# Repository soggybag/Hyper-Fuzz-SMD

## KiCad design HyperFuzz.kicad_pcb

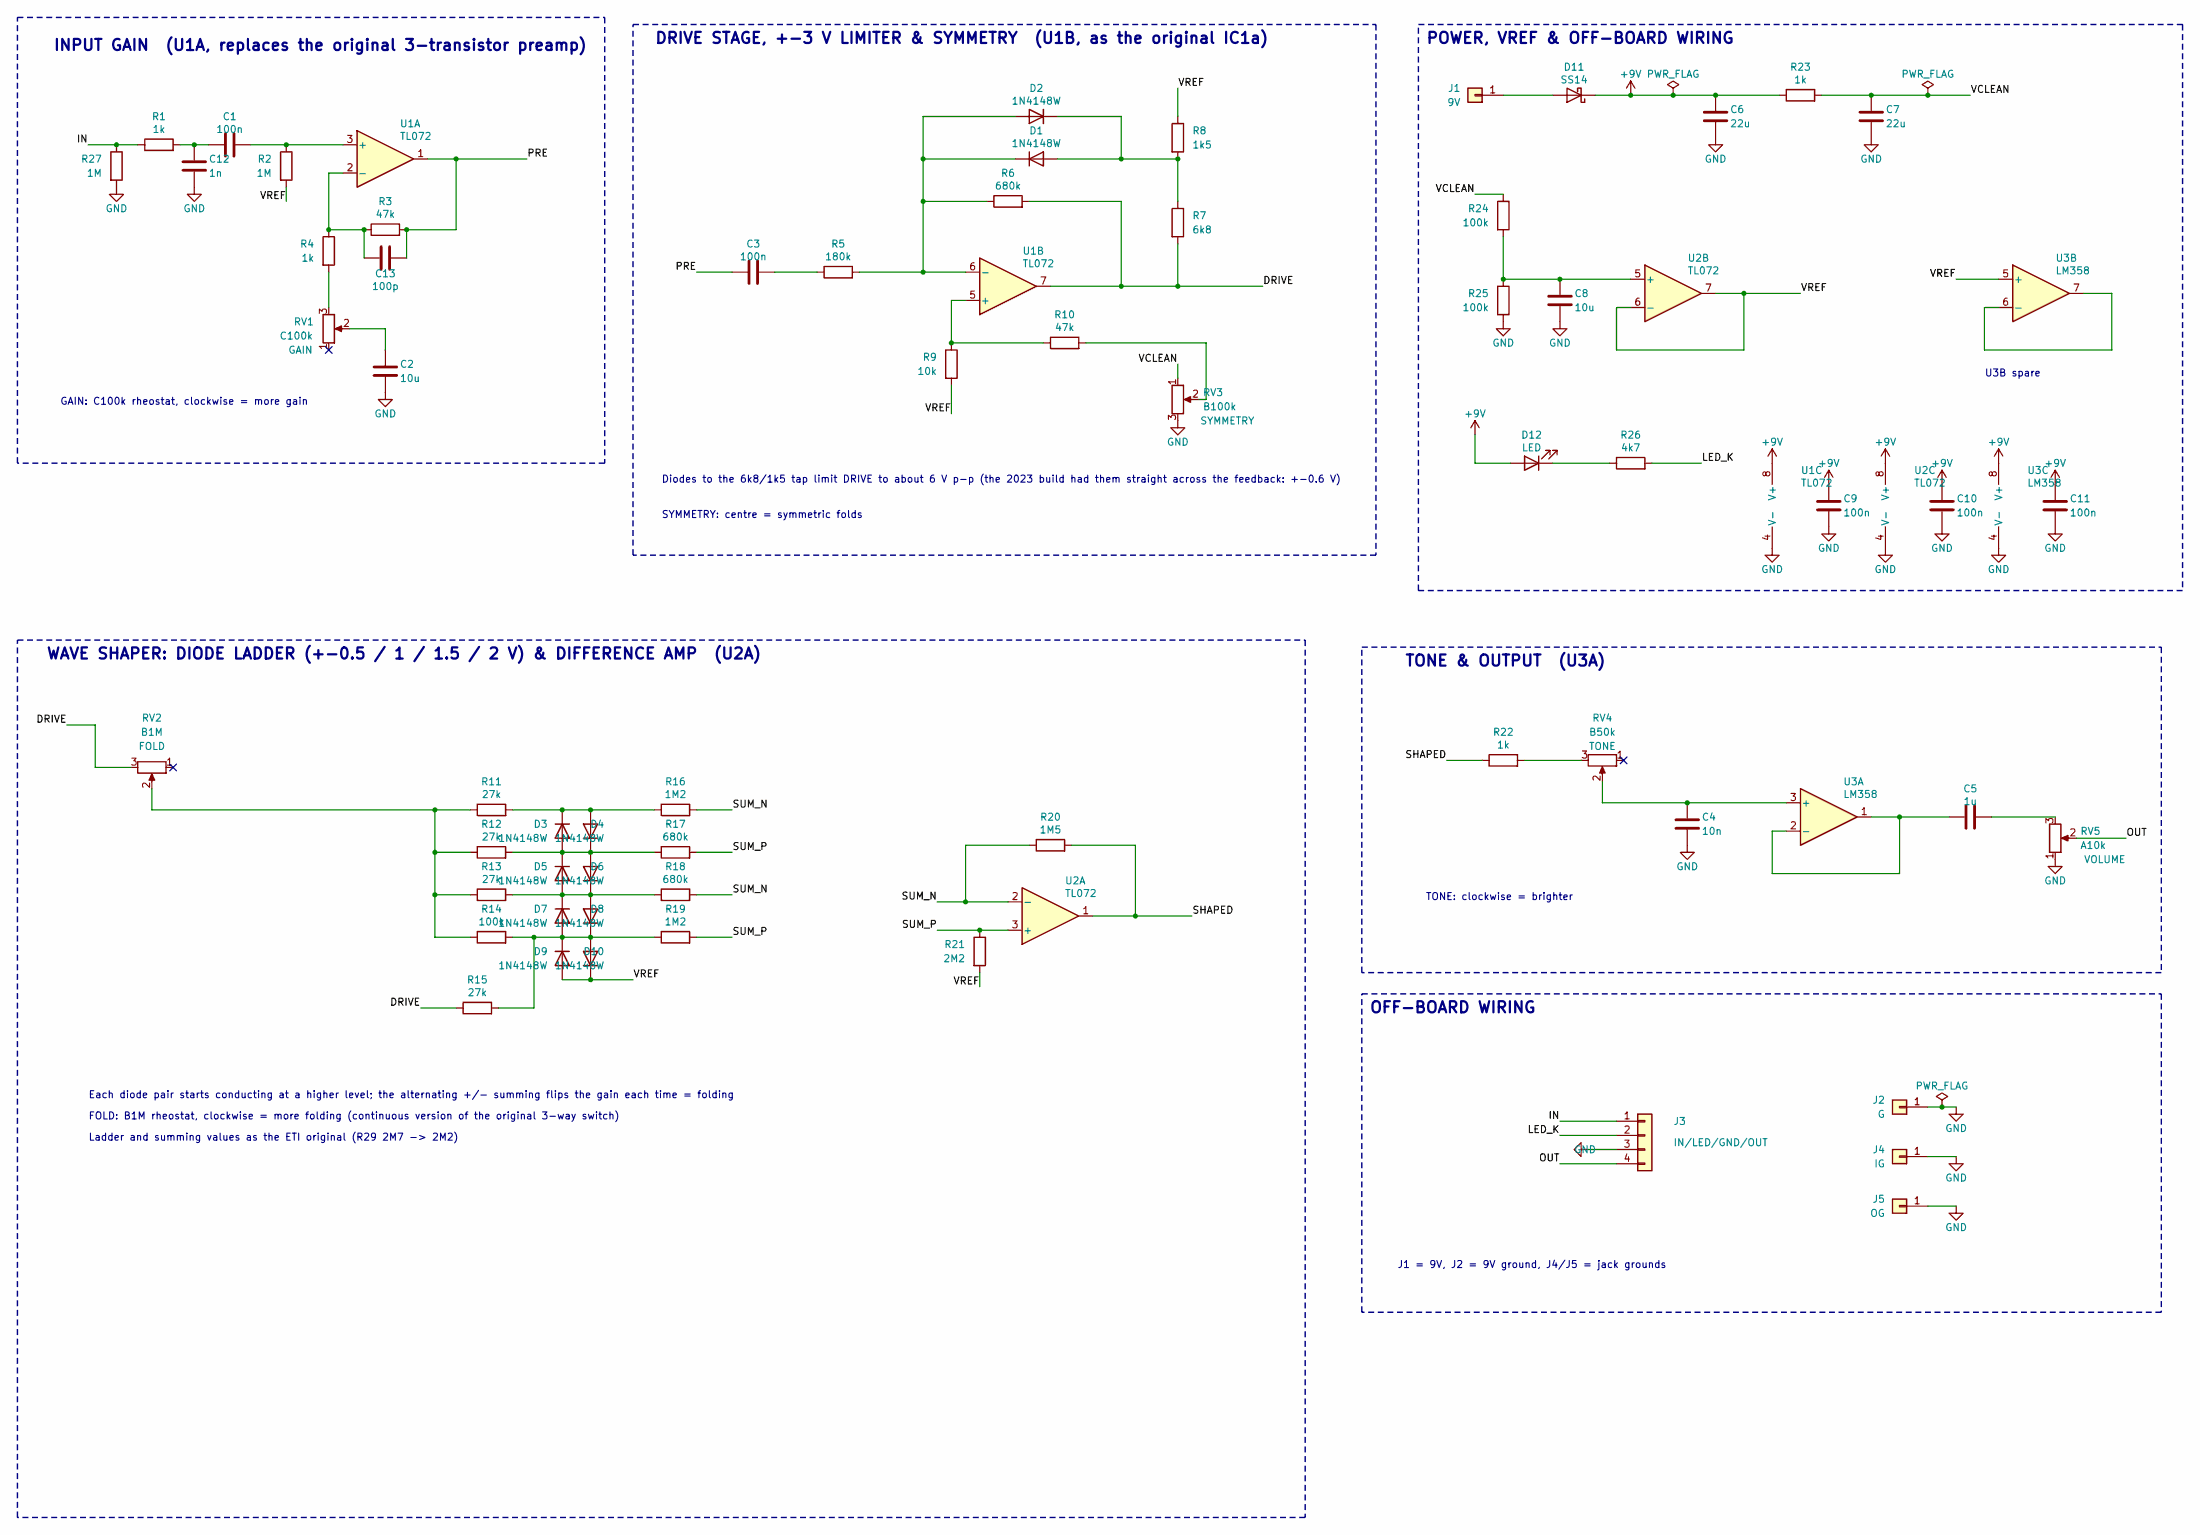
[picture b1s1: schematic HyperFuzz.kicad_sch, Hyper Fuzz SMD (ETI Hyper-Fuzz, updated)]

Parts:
C1, C3, C9, C10, C11: 100n; C_0805_2012Metric_Pad1.18x1.45mm_HandSolder; LCSC C49678
C2, C8: 10u; C_0805_2012Metric_Pad1.18x1.45mm_HandSolder; LCSC C15850
C4: 10n; C_0805_2012Metric_Pad1.18x1.45mm_HandSolder; LCSC C1710
C5: 1u; C_0805_2012Metric_Pad1.18x1.45mm_HandSolder; LCSC C28323
C6, C7: 22u; C_1206_3216Metric_Pad1.33x1.80mm_HandSolder; LCSC C12891
C12: 1n; C_0805_2012Metric_Pad1.18x1.45mm_HandSolder; LCSC C46653
C13: 100p; C_0805_2012Metric_Pad1.18x1.45mm_HandSolder; LCSC C1790
D1, D2, D3, D4, D5, D6, D7, D8, D9, D10: 1N4148W; D_SOD-123; LCSC C81598
D11: SS14; D_SMA_Handsoldering; LCSC C2480
D12: LED; LED_D3.0mm
J1: 9V; SolderWire-0.5sqmm_1x01_D0.9mm_OD2.1mm
J2: G; SolderWire-0.5sqmm_1x01_D0.9mm_OD2.1mm
J3: IN/LED/GND/OUT; PinHeader_1x04_P2.54mm_Vertical
J4: IG; SolderWire-0.5sqmm_1x01_D0.9mm_OD2.1mm
J5: OG; SolderWire-0.5sqmm_1x01_D0.9mm_OD2.1mm
R1, R4, R22, R23: 1k; R_0805_2012Metric_Pad1.20x1.40mm_HandSolder; LCSC C17513
R2, R27: 1M; R_0805_2012Metric_Pad1.20x1.40mm_HandSolder; LCSC C17514
R3, R10: 47k; R_0805_2012Metric_Pad1.20x1.40mm_HandSolder; LCSC C17713
R5: 180k; R_0805_2012Metric_Pad1.20x1.40mm_HandSolder; LCSC C17501
R6, R17, R18: 680k; R_0805_2012Metric_Pad1.20x1.40mm_HandSolder; LCSC C17797
R7: 6k8; R_0805_2012Metric_Pad1.20x1.40mm_HandSolder; LCSC C17772
R8: 1k5; R_0805_2012Metric_Pad1.20x1.40mm_HandSolder; LCSC C4310
R9: 10k; R_0805_2012Metric_Pad1.20x1.40mm_HandSolder; LCSC C17414
R11, R12, R13, R15: 27k; R_0805_2012Metric_Pad1.20x1.40mm_HandSolder; LCSC C17593
R14, R24, R25: 100k; R_0805_2012Metric_Pad1.20x1.40mm_HandSolder; LCSC C149504
R16, R19: 1M2; R_0805_2012Metric_Pad1.20x1.40mm_HandSolder; LCSC C17380
R20: 1M5; R_0805_2012Metric_Pad1.20x1.40mm_HandSolder; LCSC C26110
R21: 2M2; R_0805_2012Metric_Pad1.20x1.40mm_HandSolder; LCSC C26113
R26: 4k7; R_0805_2012Metric_Pad1.20x1.40mm_HandSolder; LCSC C17673
RV1: C100k; Potentiometer_Alpha_RD901F-40-00D_Single_Vertical
RV2: B1M; Potentiometer_Alpha_RD901F-40-00D_Single_Vertical
RV3: B100k; Potentiometer_Alpha_RD901F-40-00D_Single_Vertical
RV4: B50k; Potentiometer_Alpha_RD901F-40-00D_Single_Vertical
RV5: A10k; Potentiometer_Alpha_RD901F-40-00D_Single_Vertical
U1, U2: TL072; SOIC-8_3.9x4.9mm_P1.27mm; LCSC C6961
U3: LM358; SOIC-8_3.9x4.9mm_P1.27mm; LCSC C7950

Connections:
/DRIVE: R6.2, R7.2, R15.1, RV2.3, U1.7
/IN: J3.1, R1.1, R27.1
/LED_K: J3.2, R26.2
/OUT: J3.4, RV5.2
/PRE: C3.1, C13.2, R3.2, U1.1
/SHAPED: R20.2, R22.1, U2.1
/SUM_N: R16.2, R18.2, R20.1, U2.2 (-)
/SUM_P: R17.2, R19.2, R21.1, U2.3 (+)
/VREF: D9.2 (A), D10.1 (K), R2.2, R8.1, R9.2, R21.2, U2.6 (-), U2.7, U3.5 (+)
unnamed: C1.1, C12.1, R1.2
unnamed: C2.1, RV1.2
unnamed: C3.2, R5.1
unnamed: C5.2, RV5.3
unnamed: D1.2 (A), D2.1 (K), R7.1, R8.2
unnamed: D1.1 (K), D2.2 (A), R5.2, R6.1, U1.6 (-)
unnamed: D3.2 (A), D4.1 (K), D5.1 (K), D6.2 (A), R12.2, R17.1
unnamed: D3.1 (K), D4.2 (A), R11.2, R16.1
unnamed: D5.2 (A), D6.1 (K), D7.1 (K), D8.2 (A), R13.2, R18.1
unnamed: D7.2 (A), D8.1 (K), D9.1 (K), D10.2 (A), R14.2, R15.2, R19.1
unnamed: D11.2 (A), J1.1 (Pin_1_1)
unnamed: D12.1 (K), R26.1
unnamed: R4.2, RV1.3
unnamed: R10.2, RV3.2
unnamed: R11.1, R12.1, R13.1, R14.1, RV2.2
unnamed: R22.2, RV4.3
unnamed: C1.2, R2.1, U1.3 (+)
unnamed: C13.1, R3.1, R4.1, U1.2 (-)
unnamed: R9.1, R10.1, U1.5 (+)
unnamed: C8.1, R24.2, R25.1, U2.5 (+)
unnamed: C4.1, RV4.2, U3.3 (+)
unnamed: C5.1, U3.1, U3.2 (-)
unnamed: U3.6 (-), U3.7

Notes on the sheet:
Ladder and summing values as the ETI original (R29 2M7 -> 2M2)
OFF-BOARD WIRING
U3B spare
TONE & OUTPUT (U3A)
INPUT GAIN (U1A, replaces the original 3-transistor preamp)
WAVE SHAPER: DIODE LADDER (+-0.5 / 1 / 1.5 / 2 V) & DIFFERENCE AMP (U2A)
FOLD: B1M rheostat, clockwise = more folding (continuous version of the original 3-way switch)
SYMMETRY: centre = symmetric folds
GAIN: C100k rheostat, clockwise = more gain
DRIVE STAGE, +-3 V LIMITER & SYMMETRY (U1B, as the original IC1a)
Each diode pair starts conducting at a higher level; the alternating +/- summing flips the gain each time = folding
POWER, VREF & OFF-BOARD WIRING
TONE: clockwise = brighter
Diodes to the 6k8/1k5 tap limit DRIVE to about 6 V p-p (the 2023 build had them straight across the feedback: +-0.6 V)
J1 = 9V, J2 = 9V ground, J4/J5 = jack grounds

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
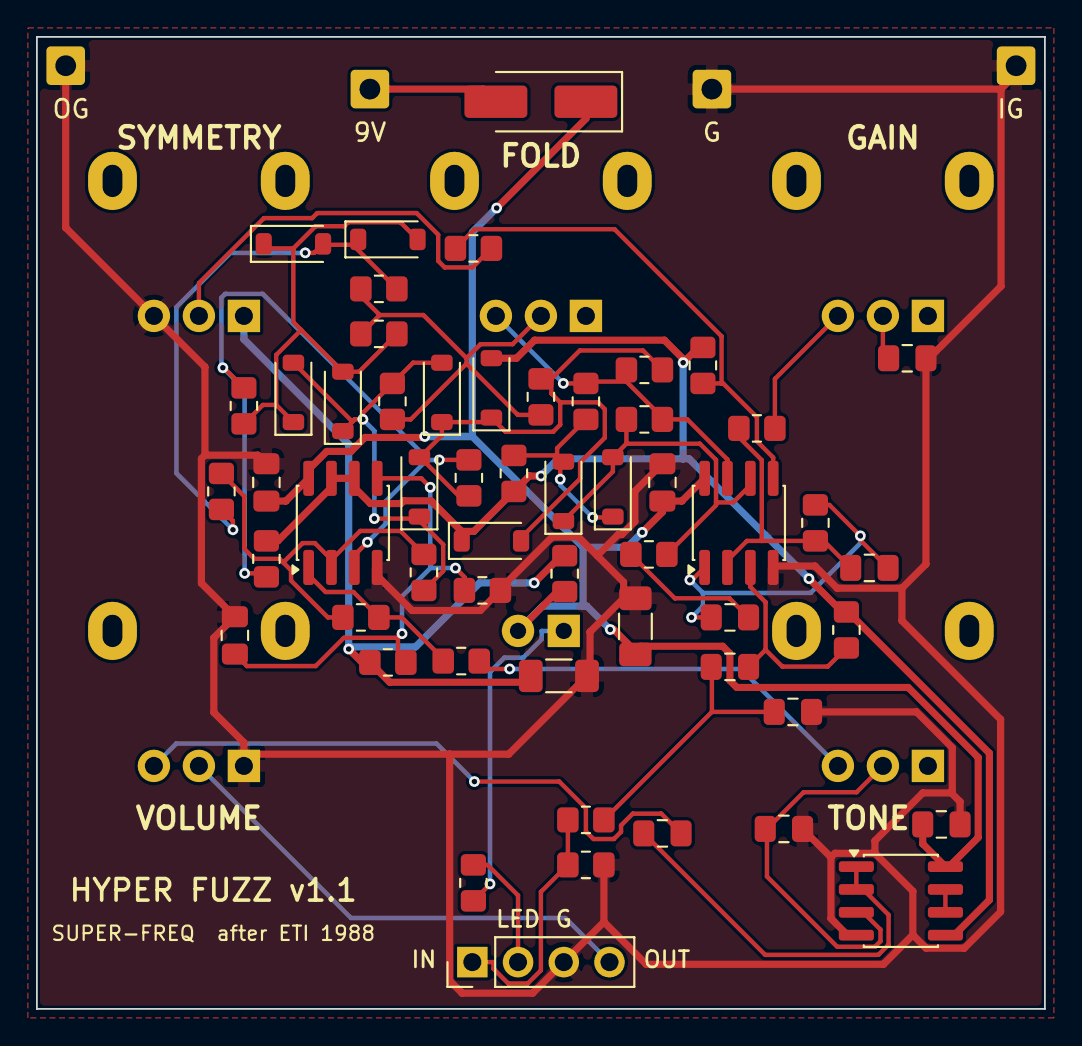
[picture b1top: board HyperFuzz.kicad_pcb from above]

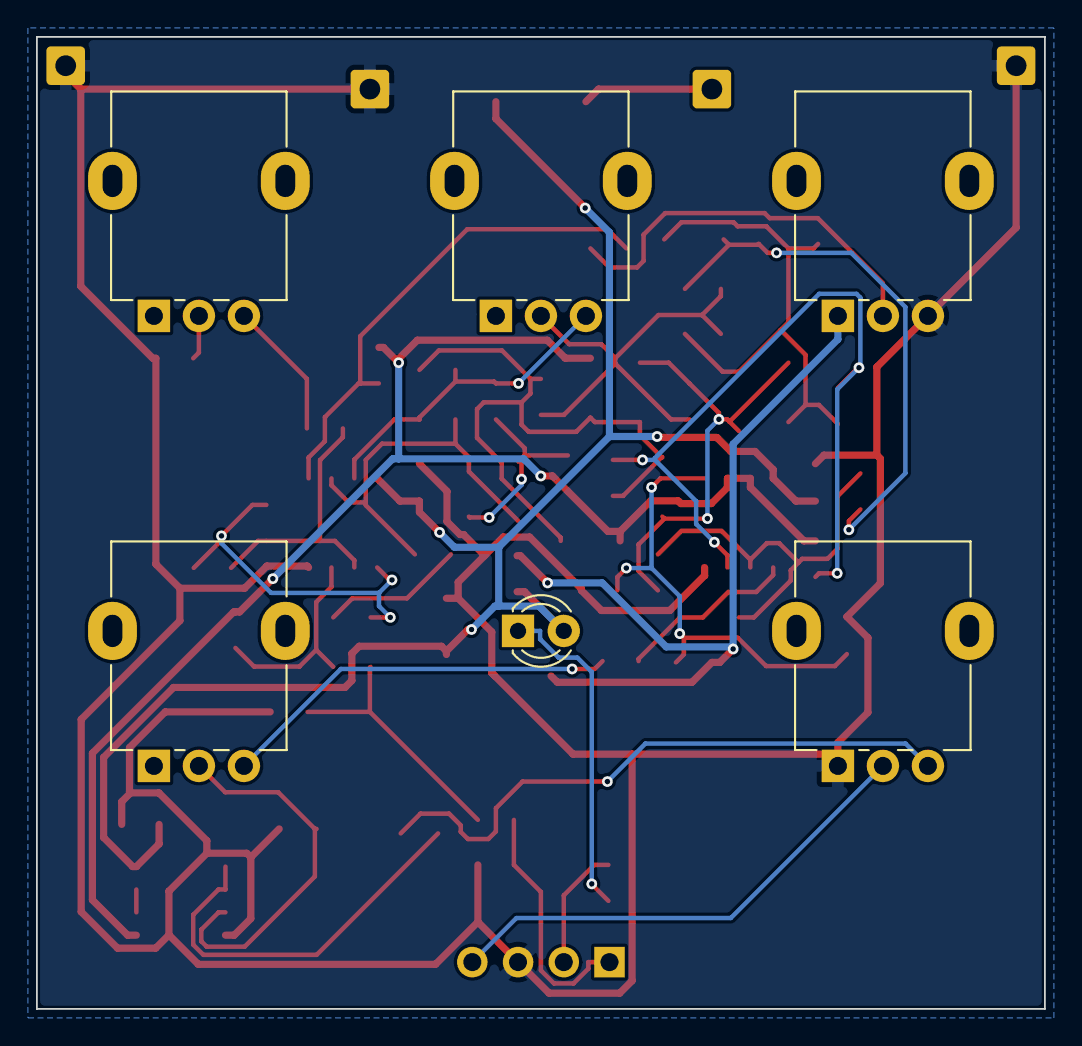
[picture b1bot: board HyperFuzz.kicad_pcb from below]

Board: 2 copper layers, 56.0 x 54.0 mm, 65 parts (6 on the bottom side), 35 nets.
